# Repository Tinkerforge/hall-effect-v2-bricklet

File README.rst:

Hall Effect Bricklet 2.0
========================

This repository contains the firmware source code and the hardware design
files. The documentation generator configs can be found at
https://github.com/Tinkerforge/generators

Repository Content
------------------

software/:
 * examples/: Examples for all supported languages
 * build/: Compiled files
 * src/: Source code of firmware
 * Makefile: Makefile to build project

hardware/:
 * Contains KiCad project files and additionally schematics as PDF

datasheets/:
 * Contains datasheets for sensors and complex ICs that are used

Hardware
--------

The hardware is designed with the open source EDA Suite KiCad
(http://www.kicad.org). Before you are able to open the files,
you have to install the Tinkerforge kicad-libraries
(https://github.com/Tinkerforge/kicad-libraries). You can either clone
them directly in hardware/ or clone them in a separate folder and
symlink them into hardware/
(ln -s kicad_path/kicad-libraries project_path/hardware). After that you
can open the .pro file in hardware/ with KiCad and from there view and
modify the schematics and the PCB layout.

Software
--------

If you want to do your own Brick/Bricklet firmware development we highly
recommend that you use our build environment setup script and read the
tutorial (https://www.tinkerforge.com/en/doc/Tutorials/Tutorial_Build_Environment/Tutorial.html).

To compile the C code we recommend you to install the newest GNU Arm Embedded
Toolchain (https://launchpad.net/gcc-arm-embedded/+download).
You also need to install bricklib2 (https://github.com/Tinkerforge/bricklib2).

You can either clone it directly in software/src/ or clone it in a
separate folder and symlink it into software/src/
(ln -s bricklib_path/bricklib2 project_path/software/src/). Finally make sure to
have CMake installed (http://www.cmake.org/cmake/resources/software.html).

After that you can build the firmware by invoking make in software/.
The firmware (.zbin) can then be found in software/build/ and uploaded
with brickv (click button "Flashing" on start screen).

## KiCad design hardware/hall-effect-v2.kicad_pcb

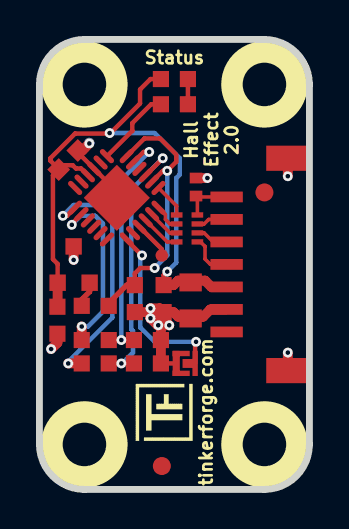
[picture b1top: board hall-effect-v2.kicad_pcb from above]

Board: 2 copper layers, 15.0 x 25.0 mm, 27 parts (0 on the bottom side), 20 nets.

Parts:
C1: 220pF; C0402F
C2: 10uF; C0805
C3: 1uF; C0603F
C4, C5, C6, C7, C8: 100nF; C0603F
D1: blue; D0603F
Fiducial_Mark: VAL**; Fiducial_Mark
Fiducial_Mark#2: VAL**; Fiducial_Mark
P1: CON-SENSOR2
P2: BOOT; SolderJumper
P3: DEBUG; DEBUG_PAD
R1, R2, R3: 1k; R0603F
R4: 100; R0603F
RP1: 82; 4X0402
U1: XMC1302; QFN24-4x4mm-0.5mm
U2: DRV5053; SOT23-3
U3, U4, U5, U6: DRILL; DRILL_NP
VAL: WEEE_7mm
VAL#2: CE_5mm

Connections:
GND: C1.2, C2.2, C3.2, C4.2, C5.2, C6.2, C7.2, C8.2, P1.2, P1.EP, P2.1, U1.9, U1.EXP, U2.3
unnamed: C1.1, P1.7, RP1.4
unnamed: D1.2, R3.2
unnamed: P1.4, RP1.1
unnamed: P1.5, RP1.2
unnamed: P1.6, RP1.3
unnamed: P2.2, U1.19
unnamed: P3.1, U1.21
unnamed: R1.1, U1.14
unnamed: R2.1, U1.13
unnamed: R3.1, U1.7
unnamed: R4.2, U2.2
OUT: C8.1, R4.1, U1.2, U1.6
S-CLK: RP1.7, U1.23
S-CS: RP1.8, U1.22
S-MISO: RP1.5, U1.1
S-MOSI: RP1.6, U1.24
VCC: C2.1, C3.1, C6.1, C7.1, D1.1, P1.3, U1.10, U2.1
VOUT0: C5.1, R2.2, U1.3
VOUT1: C4.1, R1.2, U1.5

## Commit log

2018-06-27 Add datasheet
2018-06-27 Add schematic
2018-06-27 Add layout
2018-07-06 Change input pin to P0.0
2018-07-11 Fix origin
2018-07-13 Add .gitignore
2018-07-27 Add auto-generated stub firmware
2019-01-10 update sensor
2019-01-18 add analog hall sensor with 2 reference voltages
2019-01-18 add comcu logo
2019-02-15 add sym table
2019-02-22 changed processor to XMC1100
2019-02-22 changed processor to XMC1302
2019-02-27 Change MCU to XMC1300
2019-02-27 Add API and DRV5053 driver implementation
2019-02-27 Add DRV5053 datasheet
2019-02-27 Simplify counter and timer
    We only use one counter and timer for both compare matches
2019-02-27 Only use one timer and counter in config
2019-02-28 Fix mixed up edges
2019-02-28 Change default to +-2mT
2019-02-28 Add support for counter reset
2019-03-01 Remove DRV5023 datasheet (Bricklet uses 5053)
2019-03-07 change rc values for voltage generation
2019-03-28 mqtt: Fix whitespace.
2019-03-28 Add examples.
2019-04-03 Enable ADC post calibration
2019-04-30 Implement counter callback
2019-04-30 Turn logging off
2019-05-07 Apply bootloader pointer end fix to all new Bricklets
2019-05-13 add 3d data, rename
2019-05-15 fix file names
2019-05-20 Update auto-generated rust example
2019-05-20 Release Bricklet
2019-05-20 rust: Use merged imports again.
2019-05-20 examples: Fix callback counter type
2019-05-29 Disallow SPITFP interrupt to disable IRQs
    The newest version of bricklib2 disables IRQs during SPITFP
    transfers by default. This needs to be turned off for this
    Bricklet since it has higher priority IRQs that can not wait.
    For this we set the SPITFP_NOT_ALLOWED_TO_DISABLE_IRQ define.
2019-05-29 Increase version for new release (changes in bricklib2)
2019-05-29 Add rev to changelog
2019-08-22 c: Adapt to bindings changes
2020-01-13 examples: Use python3 input instead of python2 raw_input.
2020-01-13 examples: mqtt: Remove trailing whitespace.
2020-03-16 Whitespace
2020-04-07 examples: rust: Always block when calling bindings functions.
2020-08-19 Add uc examples.
2020-08-25 uc: Fix whitespace
2020-08-27 uc: Fix warnings.
2020-08-31 uc: Use fixed-with placeholders in format strings.
2020-09-02 uc: Add example driver note.
2021-10-25 Update KiCad link
    https://www.kicad.org/blog/2021/10/Avoid-links-to-former-kicad-domain/
2022-04-19 examples: uc: Rename TF_HalContext to TF_HAL.
2022-04-27 uc: Adapt to bindings changes
2022-05-10 go: Fix format string
2022-07-06 Add license files.
2022-07-13 Fix boot pad pin
2022-07-13 Add changelog, update version
2022-07-13 Add ref for 2.0.2

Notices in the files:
hardware/hall-effect-v2.kicad_pcb:
Licensed under CERN OHL v.1.1
Copyright (©) 2018, L.Lauer
Copyright Tinkerforge GmbH 2018.
This documentation describes Open Hardware and is licensed under the
CERN OHL v. 1.1.
